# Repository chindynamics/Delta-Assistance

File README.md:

# Delta Assistance

**Delta Assistance** is an assisted mobility system designed for individuals with paralysis or reduced mobility, controlled through eye-tracking. The project combines computer vision, hardware control, and accessible design to offer a functional, low-cost, and adaptable solution. This repository contains all the code, technical documentation, and resources necessary to replicate or understand the development of the project.

## CONTENT

Below are the sections available to explore the project in more detail:  
- [Introduction](https://github.com/chindynamics/Delta-Assistance/blob/main/docs/en/1.-%20introduction.md): context, motivation, and project objectives.  
- [Installation](https://github.com/chindynamics/Delta-Assistance/blob/main/docs/en/2.-%20installation.md): step-by-step guide to clone the repository, install dependencies, and run the system.  
- [Documentation](https://github.com/chindynamics/Delta-Assistance/blob/main/docs/en/3.-%20documentation.md): full technical explanation of the design, integration, and validation process.

## FEATURES

The Delta Assistance system is designed to be accessible, modular, and adaptable. Its main innovation lies in the use of computer vision to interpret the user's gaze direction and convert it into commands to move a powered wheelchair. The eye-tracking interface was developed in Python based on Jason Orlosky's open-source code, while motion control was implemented on an Arduino Mega microcontroller using C++. This combination enables efficient communication between the user and the machine, even without physical contact.

In addition to the eye-tracking interface, a custom circuit board was designed to control the wheelchair motors, and a physical structure was adapted to integrate with a conventional wheelchair. The system is capable of recognizing five commands: move forward, move backward, turn left, turn right, and stop. Its design takes into account real-world environments, including varying lighting conditions and physical interference.

## COLLABORATION

This project was developed by the Delta Assistance team:

- [@chindynamics](https://github.com/chindynamics) – Lead on computer vision pipeline and human–computer interaction design.
- [@Sarao2341](https://github.com/Sarao2341) – Responsible for 3D modeling and mechanical integration.
- [@reginaruizz](https://github.com/reginaruizz) – PCB schematic and layout. Selected components for the power regulation stages.
- [@Ulin78](https://github.com/Ulin78) – Electronics integration and firmware support. Assisted with PCB bring-up.
- [@haydeevazquez](https://github.com/haydeevazquez) – Sound processing and obstacle detection.
- [@mirelyyc](https://github.com/mirelyyc) – UI and iconography designer. Created the visual assets for the desktop interface.

If you're interested in improving this system, adapting it to new needs, or contributing your expertise in software, hardware, or accessible design, you're welcome to collaborate. You can do so by opening an issue to report problems or suggestions, or by submitting a pull request with specific improvements. This project may also serve as an educational or research base for further developments in biomedical engineering and assistive technologies.

## LICENSE

This project is distributed under the [MIT License](https://github.com/chindynamics/Delta-Assistance/blob/main/LICENSE), meaning you are free to use, modify, and redistribute the code and resources shared here, as long as proper credit is given to the original authors.

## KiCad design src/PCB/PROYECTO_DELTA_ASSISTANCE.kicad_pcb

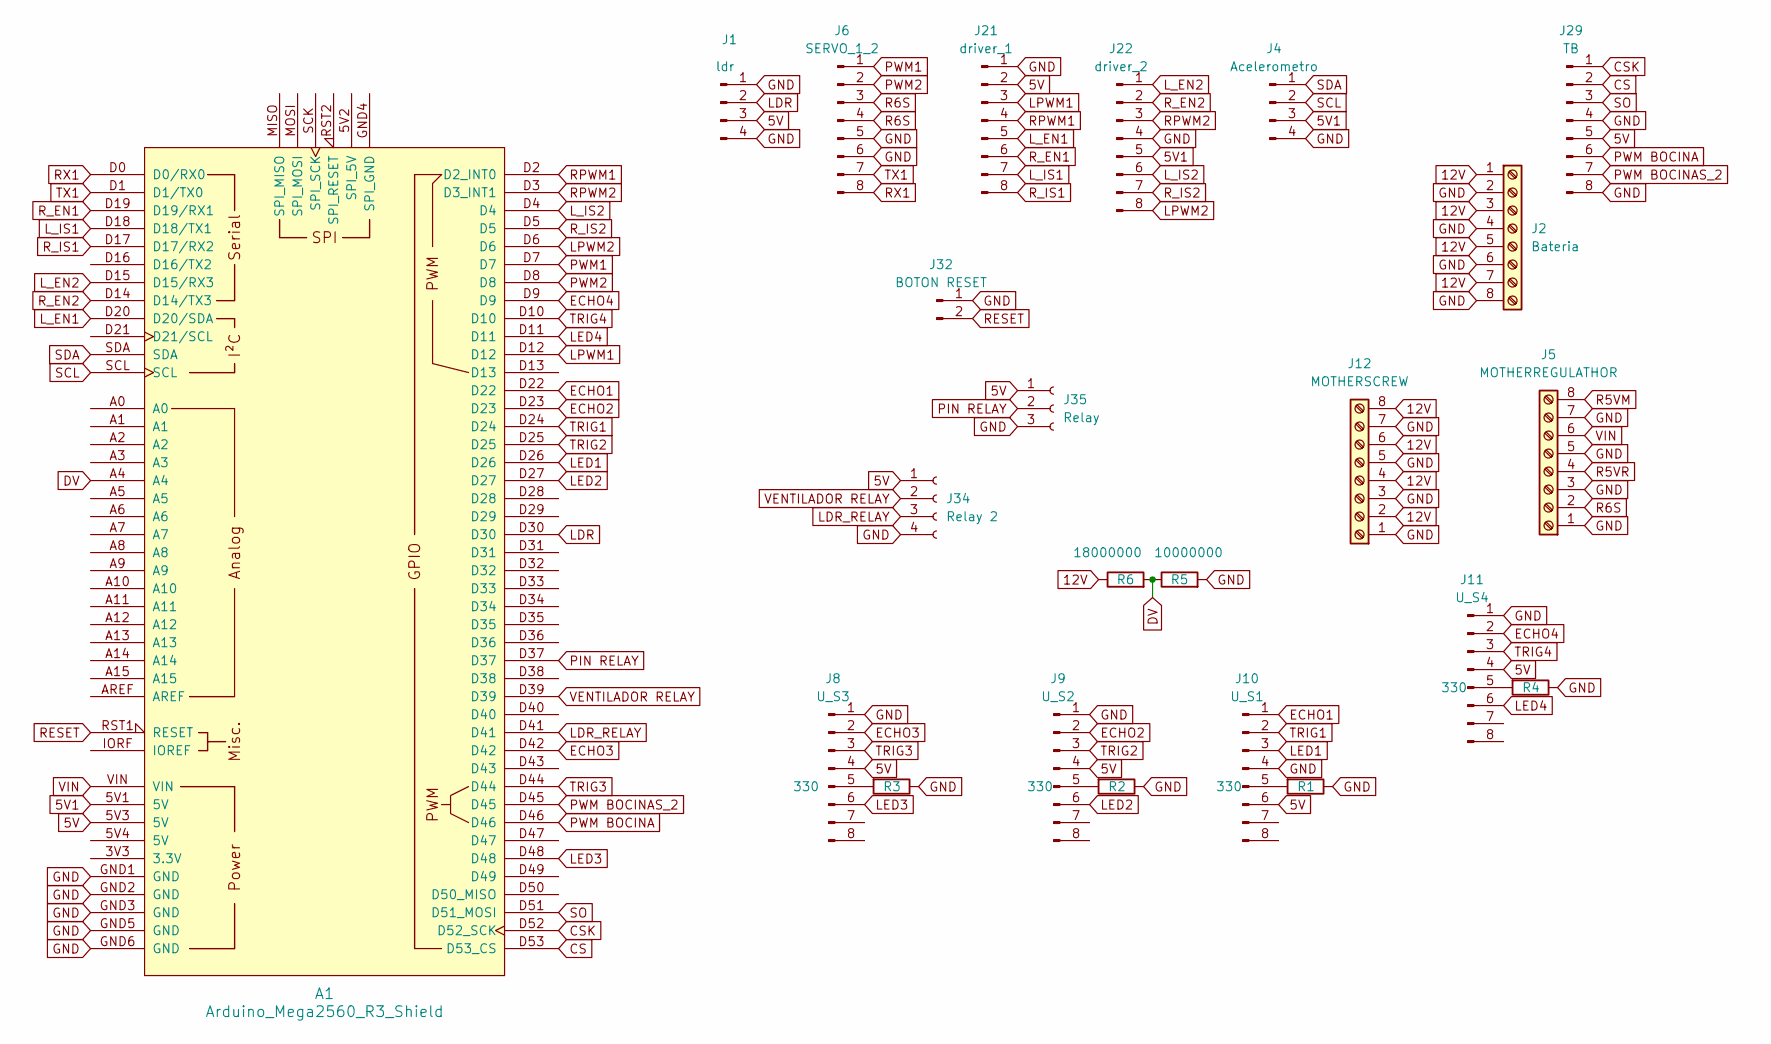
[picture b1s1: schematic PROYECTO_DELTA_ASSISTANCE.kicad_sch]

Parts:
A1: Arduino_Mega2560_R3_Shield
J1: ldr; JST_XH_B4B-XH-A_1x04_P2.50mm_Vertical
J2: Bateria; TerminalBlock_Phoenix_MKDS-1,5-8-5.08_1x08_P5.08mm_Horizont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
J4: Acelerometro; JST_XH_B4B-XH-A_1x04_P2.50mm_Vertical
J5: MOTHERREGULATHOR; TerminalBlock_Phoenix_MKDS-1,5-8-5.08_1x08_P5.08mm_Horizont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
J6: SERVO_1_2; JST_XH_B8B-XH-A_1x08_P2.50mm_Vertical
J8: U_S3; JST_XH_B8B-XH-A_1x08_P2.50mm_Vertical
J9: U_S2; JST_XH_B8B-XH-A_1x08_P2.50mm_Vertical
J10: U_S1; JST_XH_B8B-XH-A_1x08_P2.50mm_Vertical
J11: U_S4; JST_XH_B8B-XH-A_1x08_P2.50mm_Vertical
J12: MOTHERSCREW; TerminalBlock_Phoenix_MKDS-1,5-8-5.08_1x08_P5.08mm_Horizont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
J21: driver_1; JST_XH_B8B-XH-A_1x08_P2.50mm_Vertical
J22: driver_2; JST_XH_B8B-XH-A_1x08_P2.50mm_Vertical
J29: TB; JST_XH_B8B-XH-A_1x08_P2.50mm_Vertical
J32: BOTON RESET; JST_XH_B2B-XH-A_1x02_P2.50mm_Vertical
J34: Relay 2; PinHeader_1x04_P2.54mm_Vertical
J35: Relay; PinHeader_1x03_P2.54mm_Vertical
R1, R2, R3, R4: 330; R_Axial_DIN0207_L6.3mm_D2.5mm_P10.16mm_Horizontal
R5: 10000000; R_Axial_DIN0207_L6.3mm_D2.5mm_P10.16mm_Horizontal
R6: 18000000; R_Axial_DIN0207_L6.3mm_D2.5mm_P10.16mm_Horizontal

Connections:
5V: A1.5V3 (5V), J1.3, J8.4, J9.4, J10.6, J11.4, J21.2, J29.5, J34.1, J35.1
5V1: A1.5V1 (5V), J4.3, J22.5
12V: J2.1, J2.3, J2.5, J2.7, J12.2, J12.4, J12.6, J12.8, R6.1
CS: A1.D53 (D53_CS), J29.2
CSK: A1.D52 (D52_SCK), J29.1
DV: A1.A4, R5.1, R6.2
ECHO1: A1.D22, J10.1
ECHO2: A1.D23, J9.2
ECHO3: A1.D42, J8.2
ECHO4: A1.D9, J11.2
GND: A1.GND1 (GND), A1.GND2 (GND), A1.GND3 (GND), A1.GND5 (GND), A1.GND6 (GND), J1.1, J1.4, J2.2, J2.4, J2.6, J2.8, J4.4, J5.1, J5.3, J5.5, J5.7, J6.5, J6.6, J8.1, J9.1, J10.4, J11.1, J12.1, J12.3, J12.5, J12.7, J21.1, J22.4, J29.4, J29.8, J32.1, J34.4, J35.3, R1.1, R2.1, R3.1, R4.1, R5.2
LDR: A1.D30, J1.2
LDR_RELAY: A1.D41, J34.3
LED1: A1.D26, J10.3
LED2: A1.D27, J9.6
LED3: A1.D48, J8.6
LED4: A1.D11, J11.6
LPWM1: A1.D12, J21.3
LPWM2: A1.D6, J22.8
L_EN1: A1.D20 (D20/SDA), J21.5
L_EN2: A1.D15 (D15/RX3), J22.1
L_IS1: A1.D18 (D18/TX1), J21.7
L_IS2: A1.D4, J22.6
unnamed: J8.5, R3.2
unnamed: J9.5, R2.2
unnamed: J10.5, R1.2
unnamed: J11.5, R4.2
PIN RELAY: A1.D37, J35.2
PWM1: A1.D7, J6.1
PWM2: A1.D8, J6.2
PWM BOCINA: A1.D46, J29.6
PWM BOCINAS_2: A1.D45, J29.7
R5VM: J5.8
R5VR: J5.4
R6S: J5.2, J6.3, J6.4
RESET: A1.RST1 (RESET), J32.2
RPWM1: A1.D2 (D2_INT0), J21.4
RPWM2: A1.D3 (D3_INT1), J22.3
RX1: A1.D0 (D0/RX0), J6.8
R_EN1: A1.D19 (D19/RX1), J21.6
R_EN2: A1.D14 (D14/TX3), J22.2
R_IS1: A1.D17 (D17/RX2), J21.8
R_IS2: A1.D5, J22.7
SCL: A1.SCL, J4.2
SDA: A1.SDA, J4.1
SO: A1.D51 (D51_MOSI), J29.3
TRIG1: A1.D24, J10.2
TRIG2: A1.D25, J9.3
TRIG3: A1.D44, J8.3
TRIG4: A1.D10, J11.3
TX1: A1.D1 (D1/TX0), J6.7
VENTILADOR RELAY: A1.D39, J34.2
VIN: A1.VIN, J5.6

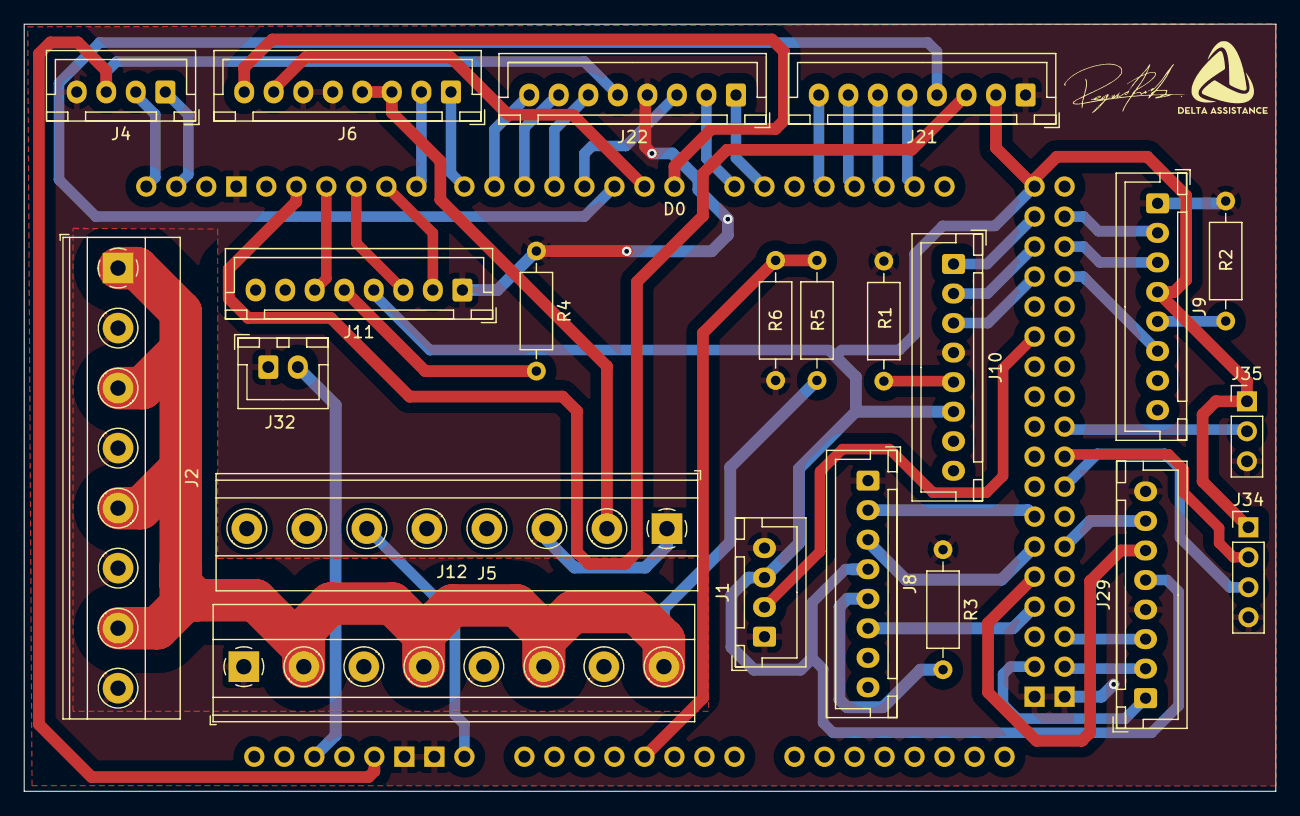
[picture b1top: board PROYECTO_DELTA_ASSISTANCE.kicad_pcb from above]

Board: 2 copper layers, 105.9 x 64.9 mm, 23 parts (0 on the bottom side), 51 nets.

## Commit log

2025-06-10 Create en
2025-06-10 Rename instalacion.md to 1.- instalacion.md
2025-06-10 Rename 1.- instalacion.md to 2.- instalacion.md
2025-06-10 Rename introduccion.md to 1.- introduccion.md
2025-06-10 updated documentation
2025-06-10 changed readme
2025-06-11 Rename introduction.md to 1.- introduction.md
2025-06-11 Create 2.- installation
2025-06-11 Update 2.- installation
2025-06-11 Rename 2.- installation to 2.- installation.md
